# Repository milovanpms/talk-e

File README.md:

<h1 align="center"></h1>

<h3 align="center">Talk-E is a walkie-talkie powered by LoRa and an ESP32-S3, operating on the 433 MHz band. And it mostly works.</h3>

<h5 align="center"><a href="https://milovan.me">milovan.me</a></h5>

## In a nutshell
- **What** : Two identical devices, one button to talk, and that's it.
- **Why** : We didn't have much time, so we wanted something original, interactive, and fun to demo. The kind of project you understand immediately just by holding it in your hands.
- **Context** : Radiocommunication student project, two-person team.

## Documentation

The documentation is quite detailed, so each part has its own page instead of having it all here.

### Find your happiness:
- ⚙️ [Hardware Architecture](./docs/architecture.md): Functional synoptic diagram and component details
- 🛠️ [Firmware](./docs/firmware.md): ESP-IDF, libraries, code architecture
- 📡 [Radio Parameters](./docs/radio.md): How we use LoRa
- 🎙️ [Audio Processing](./docs/audio.md): A voice's journey through the system
- 👤 [Human-Machine Interface](./docs/hmi.md): How does it works for the user
- 🔋 [Power Supply Circuit](./docs/power.md): Power management and energy consumption
- 🔌 [Electronics](./docs/electronics.md): Prototyping, KiCad, RF design, routing rules, our conception choices
- 📐 [Mechanical Design](./docs/cad.md): Our vision of an enclosure for this device

## Repository Structure 
```
├── hardware/        # KiCad schematics, PCB
├── firmware/        # ESP-IDF code
├── docs/            # Documentation, conception notes
├── assets/          # Images, schematics and illustrations
└── case/            # 3D models
```

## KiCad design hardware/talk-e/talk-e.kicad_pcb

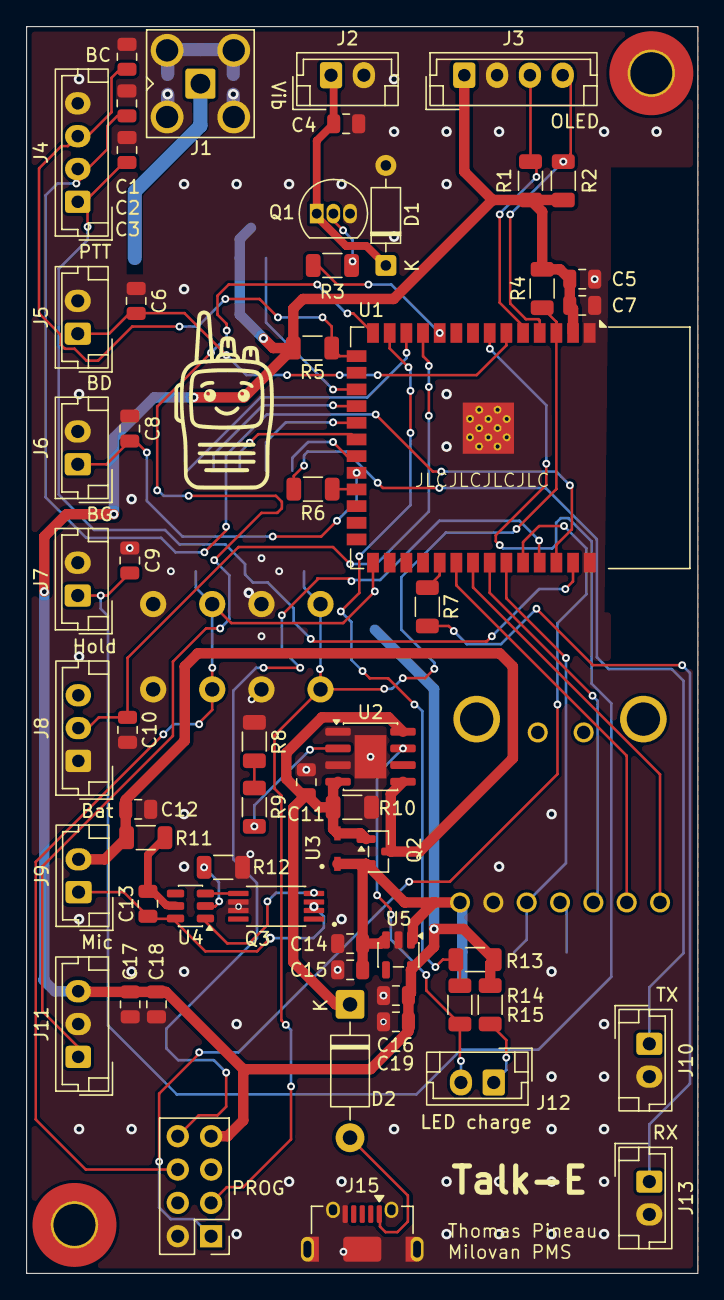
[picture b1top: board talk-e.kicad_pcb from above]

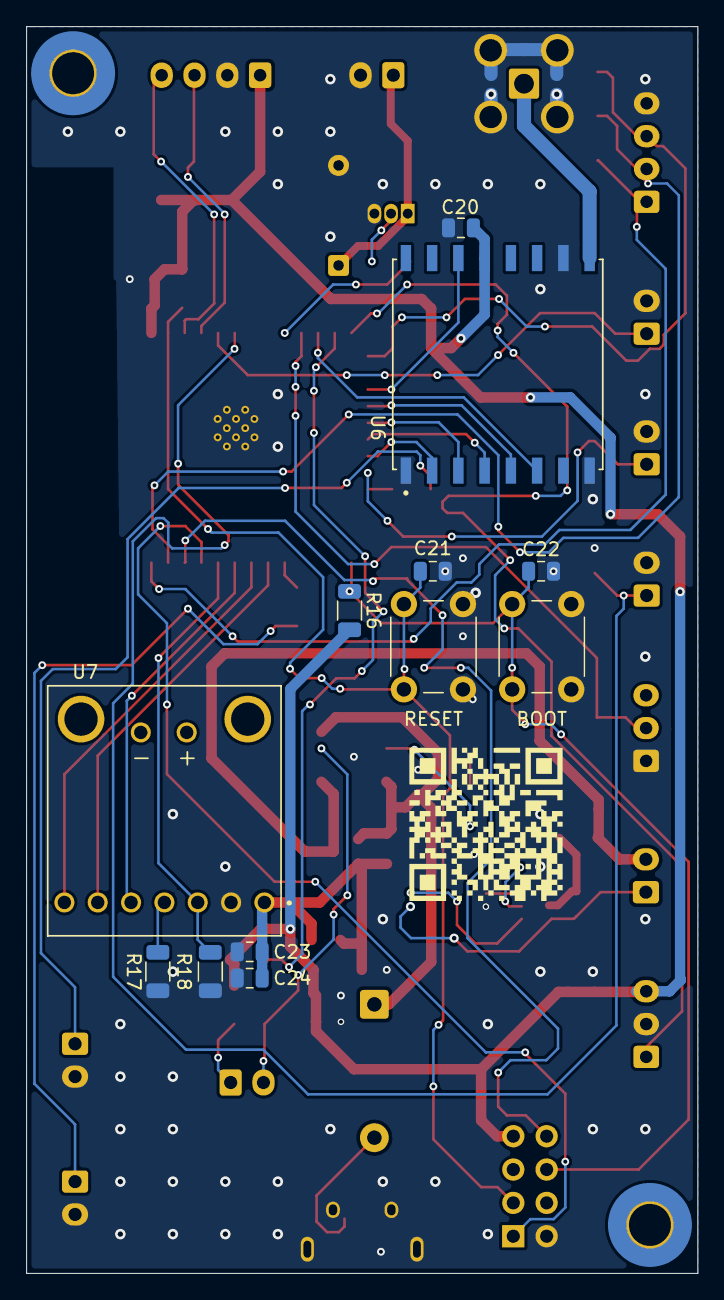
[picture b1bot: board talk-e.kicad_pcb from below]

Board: 2 copper layers, 51.1 x 95.0 mm, 71 parts (12 on the bottom side), 49 nets.

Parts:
BOOT: SW_Push; SW_PUSH_6mm
C1, C2, C3, C6, C7, C8, C9, C10, C11, C13, C15, C18, C19, C20, C21, C22, C24: 100n; C_0805_2012Metric
C4: 100µ; C_0805_2012Metric
C5, C12, C14, C16, C17: 10µ; C_0805_2012Metric
C23: 47µ; C_0805_2012Metric
D1: 1N4148; D_DO-35_SOD27_P7.62mm_Horizontal
D2: 1N5819; D_DO-41_SOD81_P10.16mm_Horizontal
J1: Conn_Coaxial; SMA_Amphenol_901-143_Horizontal
J2, J5, J6, J7, J10, J12, J13: Conn_01x02_Socket; JST_EH_B2B-EH-A_1x02_P2.50mm_Vertical
J3, J4: Conn_01x04_Socket; JST_EH_B4B-EH-A_1x04_P2.50mm_Vertical
J8, J11: Conn_01x03_Socket; JST_EH_B3B-EH-A_1x03_P2.50mm_Vertical
J9: Conn_01x02; JST_EH_B2B-EH-A_1x02_P2.50mm_Vertical
J15: USB_B_Micro; USB_Micro-AB_Molex_47590-0001
PROG: Conn_02x04_Odd_Even; PinHeader_2x04_P2.54mm_Vertical
Q1: BC337; TO-92_Inline
Q2: IRLML6402; SOT-23
Q3: FS8205A; SOP65P640X120-8N
R1, R2: 4.7k; R_1206_3216Metric
R3, R8, R9, R12: 1k; R_1206_3216Metric
R4, R5, R13, R16: 10k; R_1206_3216Metric
R6, R7, R15: 330R; R_1206_3216Metric
R10, R17, R18: 100k; R_1206_3216Metric
R11: 100R; R_1206_3216Metric
R14: 47k; R_1206_3216Metric
RESET: SW_Push; SW_PUSH_6mm
U1: ESP32-S3-WROOM-1
U2: TP4056-42-ESOP8; SOIC-8-1EP_3.9x4.9mm_P1.27mm_EP2.41x3.3mm
U3: SBR130S3-7
U4: DW01A; SOT-23-6
U5: AP2112K-3.3; SOT-23-5
U6: RFM96W-433S2; MODULE_RFM96W-433S2
U7: 3006; MODULE_3006

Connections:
+3.3V: C5.1, C7.1, C16.1, C17.1, C18.1, C19.1, C20.1, J3.1, J11.3, PROG.7, R1.2, R2.2, R4.2, R5.2, R13.1, R15.1, R16.2, U1.2 (3V3), U5.5 (VOUT), U6.13 (3.3V)
+5V: C11.1, D2.1 (K), Q2.1 (G), R10.2, U2.4 (V_{CC}), U2.8 (CE), U3.A
/ADC_MICRO: J11.1, U1.14 (USB_D+)
/B+: C12.1, J9.2, Q2.3 (D), R11.1, U2.5 (BAT)
/B-: C13.2, J9.1, Q3.2, Q3.3, U4.6 (GND)
/BTN_1: C9.1, J7.1, U1.7 (IO7)
/BTN_2: C8.1, J6.1, U1.22 (IO14)
/BTN_PTT: C6.1, J5.1, U1.6 (IO6)
/CHRG: J12.2, R14.1, U2.7 (~CHRG)
/ENC_A: C3.1, J4.1, U1.39 (IO1)
/ENC_B: C2.1, J4.2, U1.38 (IO2)
/ENC_SW: C1.1, J4.3, R5.1, U1.15 (IO3)
/GPIO_RX: R6.1, U1.23 (IO21)
/GPIO_TX: R7.1, U1.31 (IO38)
/I2C_SCL: J3.3, R1.1, U1.5 (IO5)
/I2C_SDA: J3.4, R2.1, U1.4 (IO4)
/I2S_BCLK: U1.32 (IO39), U7.JP1_6 (BCLK)
/I2S_DOUT: U1.34 (IO41), U7.JP1_5 (DIN)
/I2S_LRCLK: U1.33 (IO40), U7.JP1_7 (LRCLK)
/I2S_SD: R18.1, U1.35 (IO42), U7.JP1_3 (SD)
/J_VIB_+: C4.1, D1.1 (K), J2.1, Q1.1 (C)
/LORA_CS: U1.18 (IO10), U6.5 (NSS)
/LORA_DIO0: U1.17 (IO9), U6.14 (DIO0)
/LORA_MISO: U1.21 (IO13), U6.2 (MISO)
/LORA_MOSI: U1.19 (IO11), U6.3 (MOSI)
/LORA_RST: U1.12 (IO8), U6.6 (RESET)
/LORA_SCK: U1.20 (IO12), U6.4 (SCK)
/VBUS: D2.2 (A), J15.1 (VBUS)
/VIBREUR: R3.1, U1.10 (IO17)
ANTENNA: J1.1 (In), U6.9 (ANT)
GND: BOOT.2, C1.2, C2.2, C3.2, C4.2, C5.2, C6.2, C7.2, C8.2, C9.2, C10.2, C11.2, C12.2, C14.2, C15.2, C16.2, C17.2, C18.2, C19.2, C20.2, C21.2, C22.2, C23.2, C24.2, D1.2 (A), J1.2 (Ext), J2.2, J3.2, J4.4, J5.2, J6.2, J7.2, J8.1, J10.2, J11.2, J13.2, J15.5 (GND), J15.SH (Shield), PROG.2, Q1.3 (E), Q3.6, Q3.7, R8.2, R10.1, R12.1, R17.1, R18.2, RESET.2, U1.1 (GND), U1.40 (GND), U1.41 (GND), U2.1 (TEMP), U2.3 (GND), U2.9 (EPAD), U5.2 (GND), U6.1 (GND), U6.8 (GND), U6.10 (GND), U7.JP1_2 (GND)
GPIO0: BOOT.1, C22.1, PROG.6, R16.1, U1.27 (IO0)
GPIO_CHRG: R13.2, R14.2, U1.13 (USB_D-)
unnamed: J10.1, R6.2
unnamed: J12.1, R15.2
unnamed: J13.1, R7.2
unnamed: Q1.2 (B), R3.2
unnamed: R8.1, R9.2
unnamed: R9.1, U2.2 (PROG)
unnamed: R12.2, U4.2 (CS)
unnamed: Q3.5, U4.3 (OC)
unnamed: Q3.4, U4.1 (OD)
unnamed: C13.1, R11.2, U4.5 (VCC)
unnamed: R17.2, U7.JP1_4 (GAIN)
OUT+: C14.1, C15.1, C23.1, C24.1, Q2.2 (S), U3.C, U5.1 (VIN), U5.3 (EN), U7.JP1_1 (VDD)
RESET: C21.1, PROG.3, R4.1, RESET.1, U1.3 (EN)
RXD: PROG.8, U1.37 (TXD0)
SW_LOCK: C10.1, J8.2, U1.11 (IO18)
TXD: PROG.1, U1.36 (RXD0)

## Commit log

2026-05-04 Projects creation
2026-05-04 Add LoRa main app test
    - Add a new main.c implementing a simple LoRa application
    - The new app initializes the LoRa radio, sets frequency to 433 MHz, enables CRC, and creates FreeRTOS tasks for TX/RX behavior
2026-05-04 Add SX1278 parameters
2026-05-04 Add u8g2 library and test program oled.c
    Took library from i2c_u8g2 example ESP-IDF project
2026-05-07 Progress on battery charging schematic
    TP4056 + DW01A + FS8205A
2026-05-08 Added SX1278 connections to ESP32-S3 in schematic
2026-05-09 Added SH1106 OLED screen to schematic
2026-05-09 Added EC12 incremental encoder to schematic
2026-05-09 Added 3 buttons and power switch
2026-05-09 Added vibration motor to schematic
2026-05-09 Added RESET button and TX/RX LEDs to schematic
2026-05-09 Added RESET button and TX/RX LEDs to schematic (2)
2026-05-10 Added TP4056, DW01A, AP2112K-3.3 to schematic
2026-05-10 Added UART IDC connector, ESP32 decoupling capacitors
2026-05-10 Added SMA connector (antenna)
2026-05-10 Added crystal
2026-05-10 Something moved in the schematic but idk what
2026-05-11 Added audio libs
2026-05-11 add audio components
    add audio components
2026-05-12 Added ampli + mic + finished GPIO mapping
2026-05-12 Replaced ESP32-S3 with ESP32-S3-WROOM-1
2026-05-19 Finished routing + PCB ready for production
2026-06-15 Add logo
2026-06-15 Add logo 2
2026-06-16 Add doc files
2026-06-16 Rename ihm.md to hmi.md
2026-06-16 Moved medias to media folder
2026-06-16 Add audio.md
2026-06-18 Rename pcb.md to electronics.md
2026-06-20 Renamed media folder to assets
2026-06-20 Removed gif
2026-06-25 Removed media folder
2026-06-25 Add block diagram image
2026-06-25 Add images
2026-06-25 Add case README.md
2026-06-27 Rename cao.md to cad.md
